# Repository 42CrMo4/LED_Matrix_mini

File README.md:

# KiCad Mini LED Matrxi

Mini LED Matrix with SK6805 1515

## Description

3x3 SK6805 1515 (1.5mm x 1.5mm) Matrix with 2.54mm header pins and a data series resistor

## Goal

Status: **Finished**

Goal: **80-20-rule** - 80% outcome with 20% effort

## KiCanvas 

view the project files in the browaser without downloading or installing anything via [KiCanvas](https://kicanvas.org)

[Main branche - Development](https://kicanvas.org/?github=https%3A%2F%2Fgithub.com%2F42CrMo4%2FP006_LED_Matrix_mini)

[v1.1](https://kicanvas.org/?github=https%3A%2F%2Fgithub.com%2F42CrMo4%2FP006_LED_Matrix_mini%2Ftree%2Fv1.1)

[v1.0](https://kicanvas.org/?github=https%3A%2F%2Fgithub.com%2F42CrMo4%2FP006_LED_Matrix_mini%2Ftree%2Fv1.0)

## Description. 

| Font                                                                    | Back                                                                      |
|-------------------------------------------------------------------------|---------------------------------------------------------------------------|
|  |  |

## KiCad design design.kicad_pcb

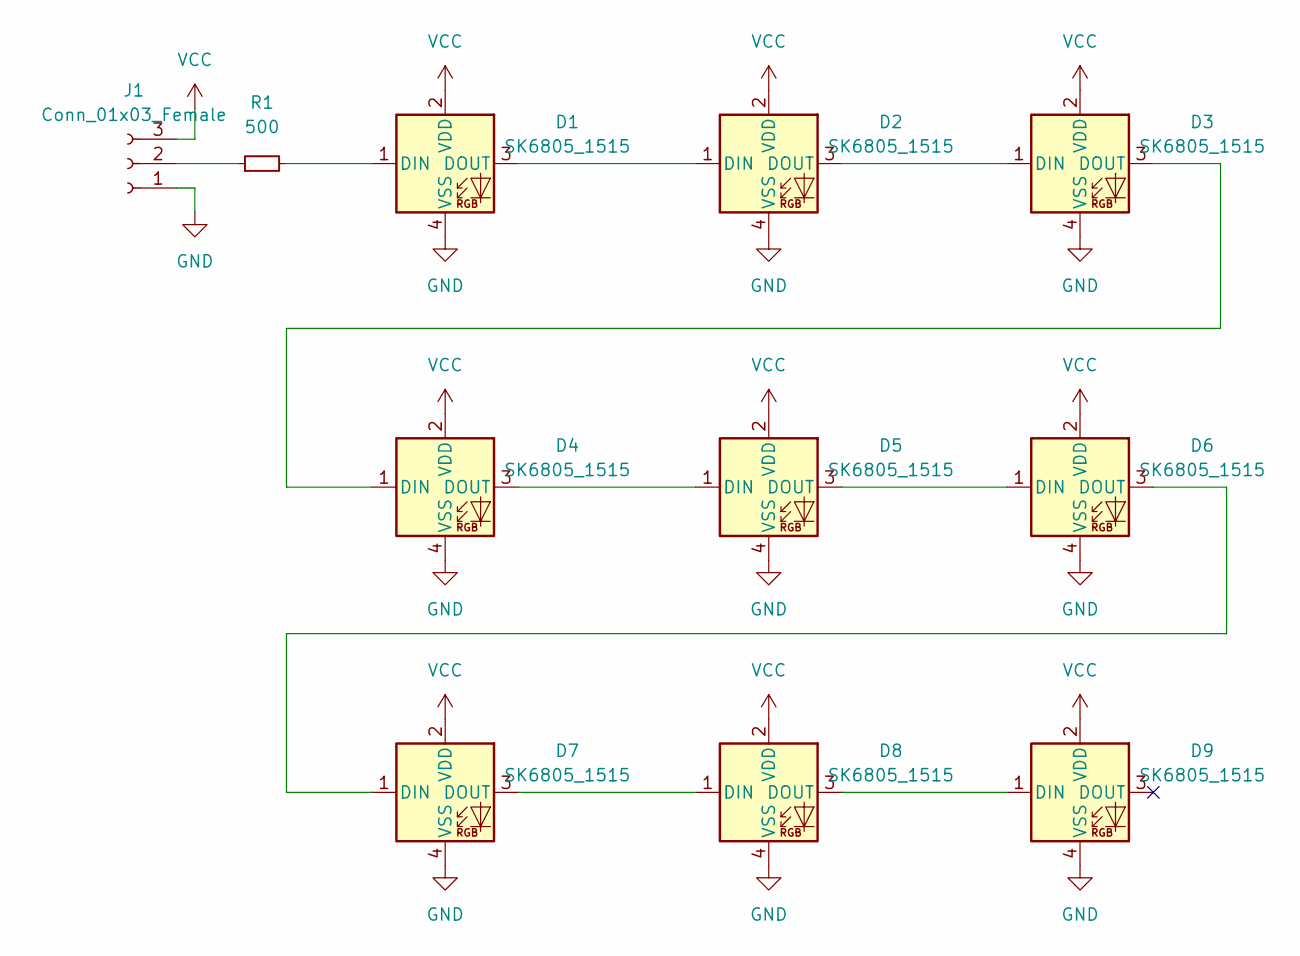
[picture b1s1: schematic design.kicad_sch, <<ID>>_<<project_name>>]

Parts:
D1, D2, D3, D4, D5, D6, D7, D8, D9: SK6805_1515; LED_SK6812_EC15_1.5x1.5mm
J1: Conn_01x03_Female; PinHeader_1x03_P2.54mm_Vertical
R1: 500; R_0805_2012Metric

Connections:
GND: D1.4 (VSS), D2.4 (VSS), D3.4 (VSS), D4.4 (VSS), D5.4 (VSS), D6.4 (VSS), D7.4 (VSS), D8.4 (VSS), D9.4 (VSS), J1.1
unnamed: D1.1 (DIN), R1.2
unnamed: D1.3 (DOUT), D2.1 (DIN)
unnamed: D2.3 (DOUT), D3.1 (DIN)
unnamed: D3.3 (DOUT), D4.1 (DIN)
unnamed: D4.3 (DOUT), D5.1 (DIN)
unnamed: D5.3 (DOUT), D6.1 (DIN)
unnamed: D6.3 (DOUT), D7.1 (DIN)
unnamed: D7.3 (DOUT), D8.1 (DIN)
unnamed: D8.3 (DOUT), D9.1 (DIN)
unnamed: J1.2, R1.1
VCC: D1.2 (VDD), D2.2 (VDD), D3.2 (VDD), D4.2 (VDD), D5.2 (VDD), D6.2 (VDD), D7.2 (VDD), D8.2 (VDD), D9.2 (VDD), J1.3

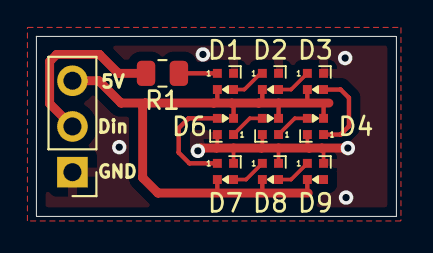
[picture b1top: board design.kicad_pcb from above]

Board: 2 copper layers, 20.0 x 10.0 mm, 11 parts (0 on the bottom side), 12 nets.

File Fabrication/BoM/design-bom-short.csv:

Row,Description,Part,References,Value,Footprint,Quantity Per PCB,Status,Datasheet
1,RGB LED with integrated controller,SK6805_1515,D1 D2 D3 D4 D5 D6 D7 D8 D9,SK6805_1515,LED_SK6812_EC15_1.5x1.5mm,9, ,https://datasheet.lcsc.com/lcsc/2108251530_OPSCO-Optoelectro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
2,"Generic connector, single row, 01x03, script generated (kicad-library-utils/schlib/autogen/connector/)",Conn_01x03_Female,J1,Conn_01x03_Female,PinHeader_1x03_P2.54mm_Vertical,1, ,~
3,"Resistor, small symbol",R_Small,R1,500,R_0805_2012Metric,1, ,~

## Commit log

2022-12-30 DEL Template stuff
2022-12-30 first layouts
2022-12-30 scramble
2022-12-30 more initial layout
2022-12-30 changed to custom sk6805 footprint
2022-12-30 3d view zoom level
2022-12-30 error from ERC
2022-12-30 erros DRC
2022-12-30 Update Bom and PCB_top
2022-12-30 release checklist und note
2022-12-30 Archive & Renew release docs
2025-01-19 Update README.md
    add
    - Description
    - Goal
    - Kicanvas Links
2025-01-19 PCB cleanup
    no functional changes.
2025-01-19 kibot 1.8.2
2025-01-19 1.8.1?
2025-01-19 kibot 1.8.1 works
    includes KiDiff also right now latest tag.
2025-01-19 actions/checkout@v4
2025-01-19 actions/upload-artifact@v4
2025-01-19 vimtor/action-zip@v1
    use v1.x
2025-01-19 stefanzweifel/git-auto-commit-action@v5
2025-01-19 add more GND vias
2025-01-19 DRC Error fix
2025-01-19 Move via down for better fit with silkscreen
2025-01-19 move vias
